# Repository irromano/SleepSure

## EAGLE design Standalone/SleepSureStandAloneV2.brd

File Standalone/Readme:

This folder includes the EAGLE files for the standalone Sleepsure circuit.

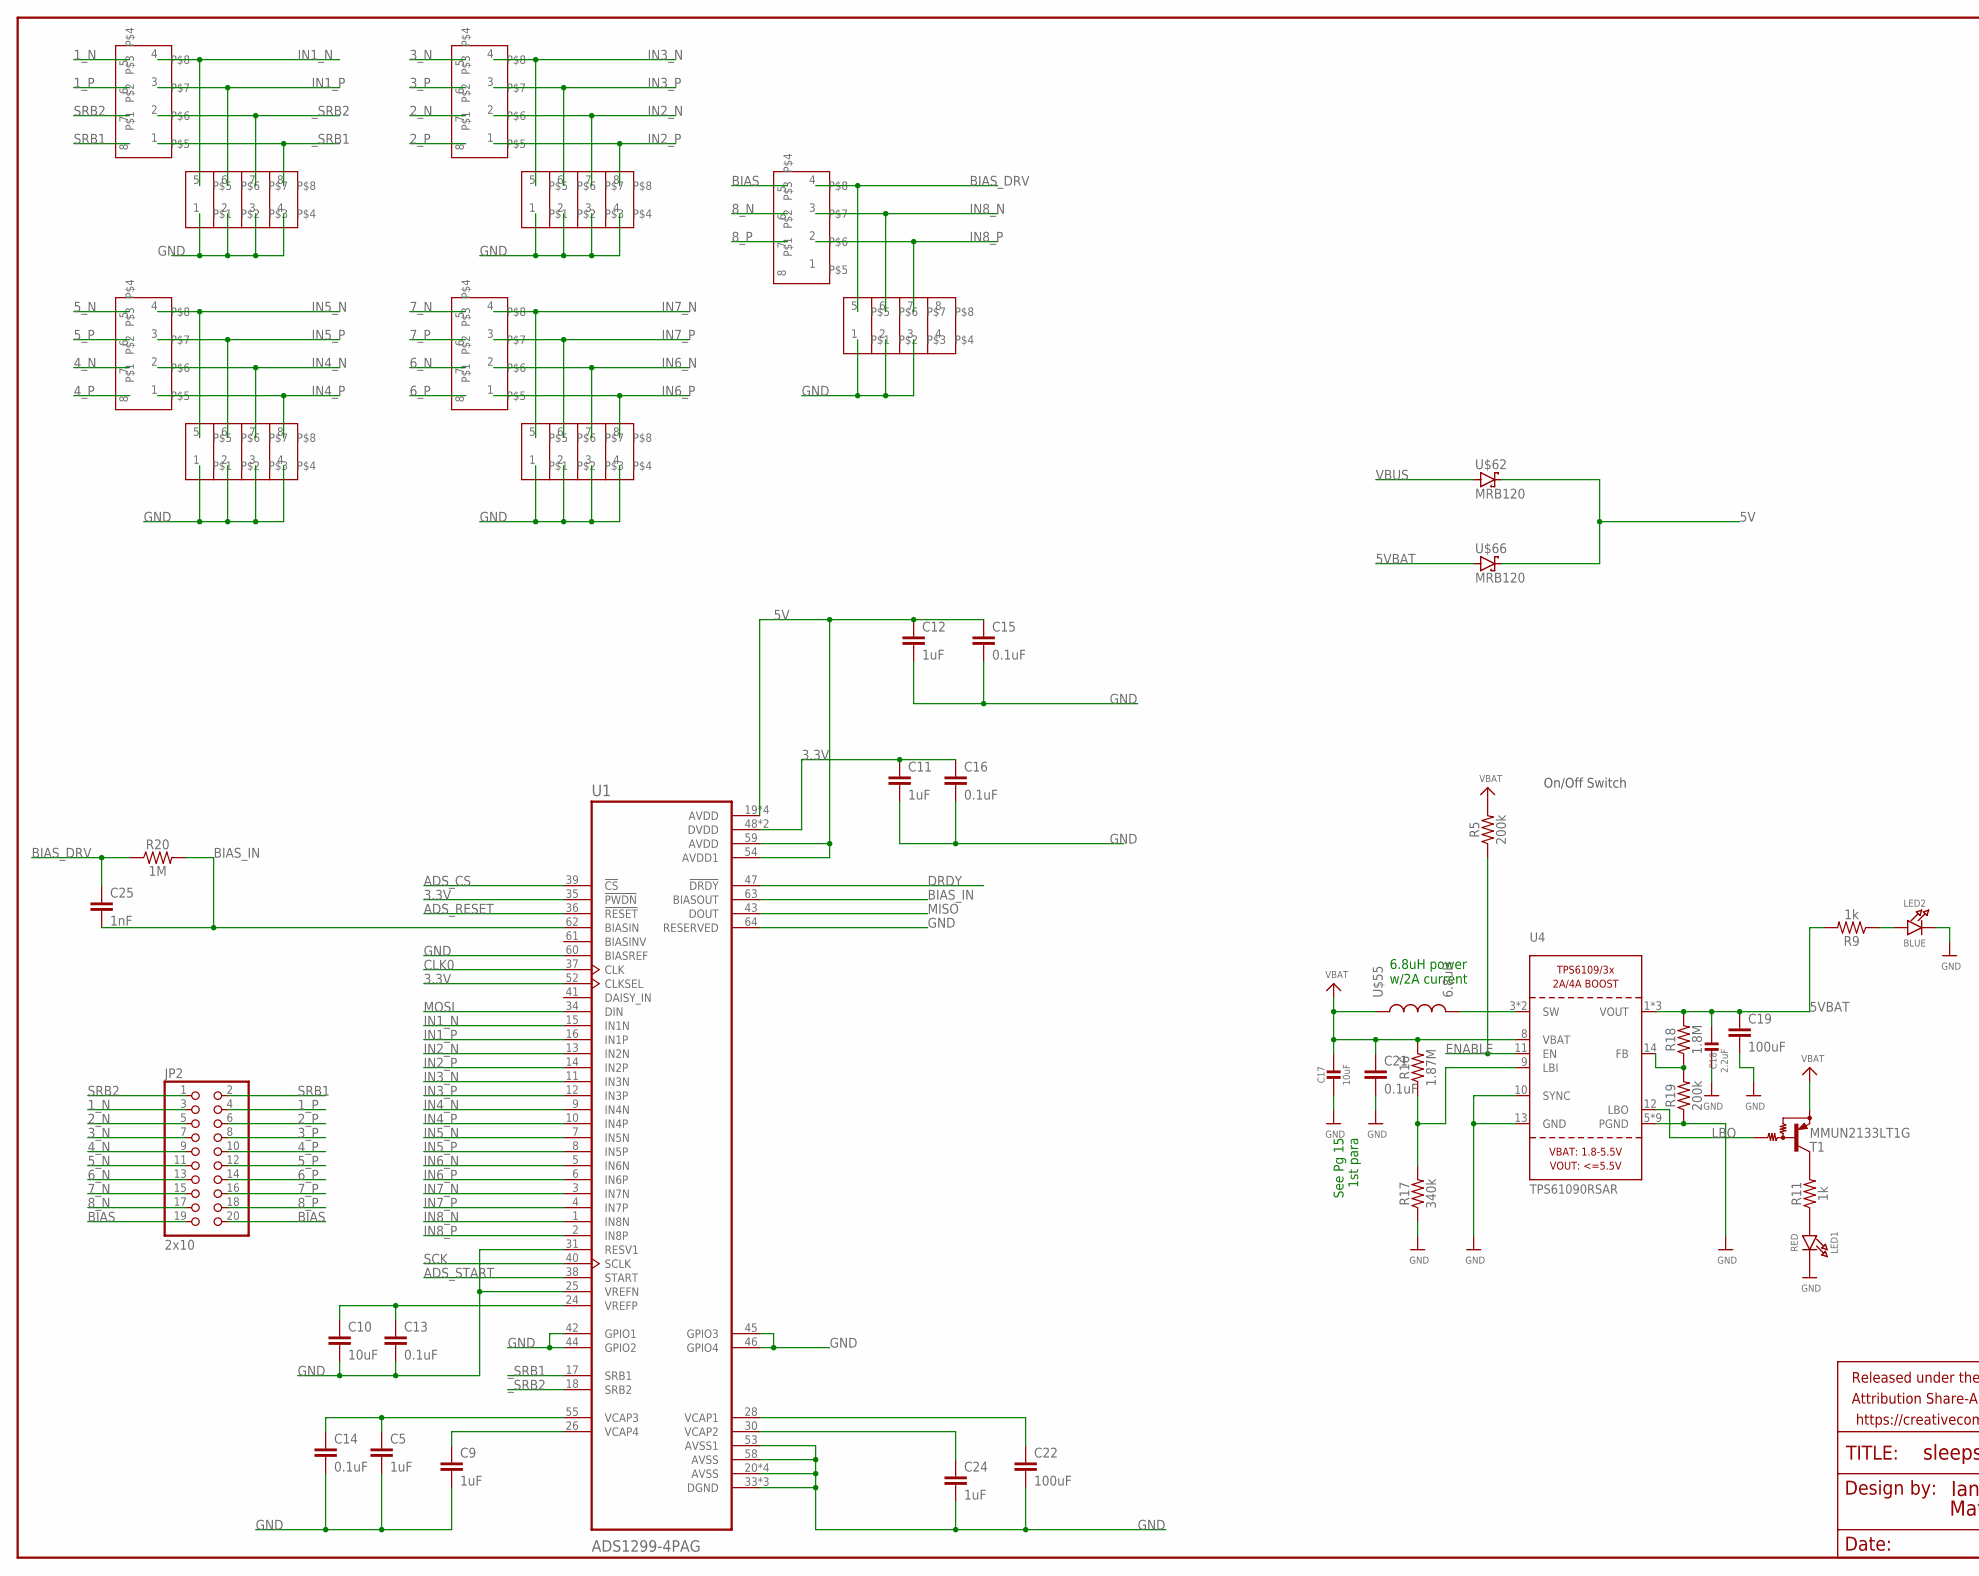
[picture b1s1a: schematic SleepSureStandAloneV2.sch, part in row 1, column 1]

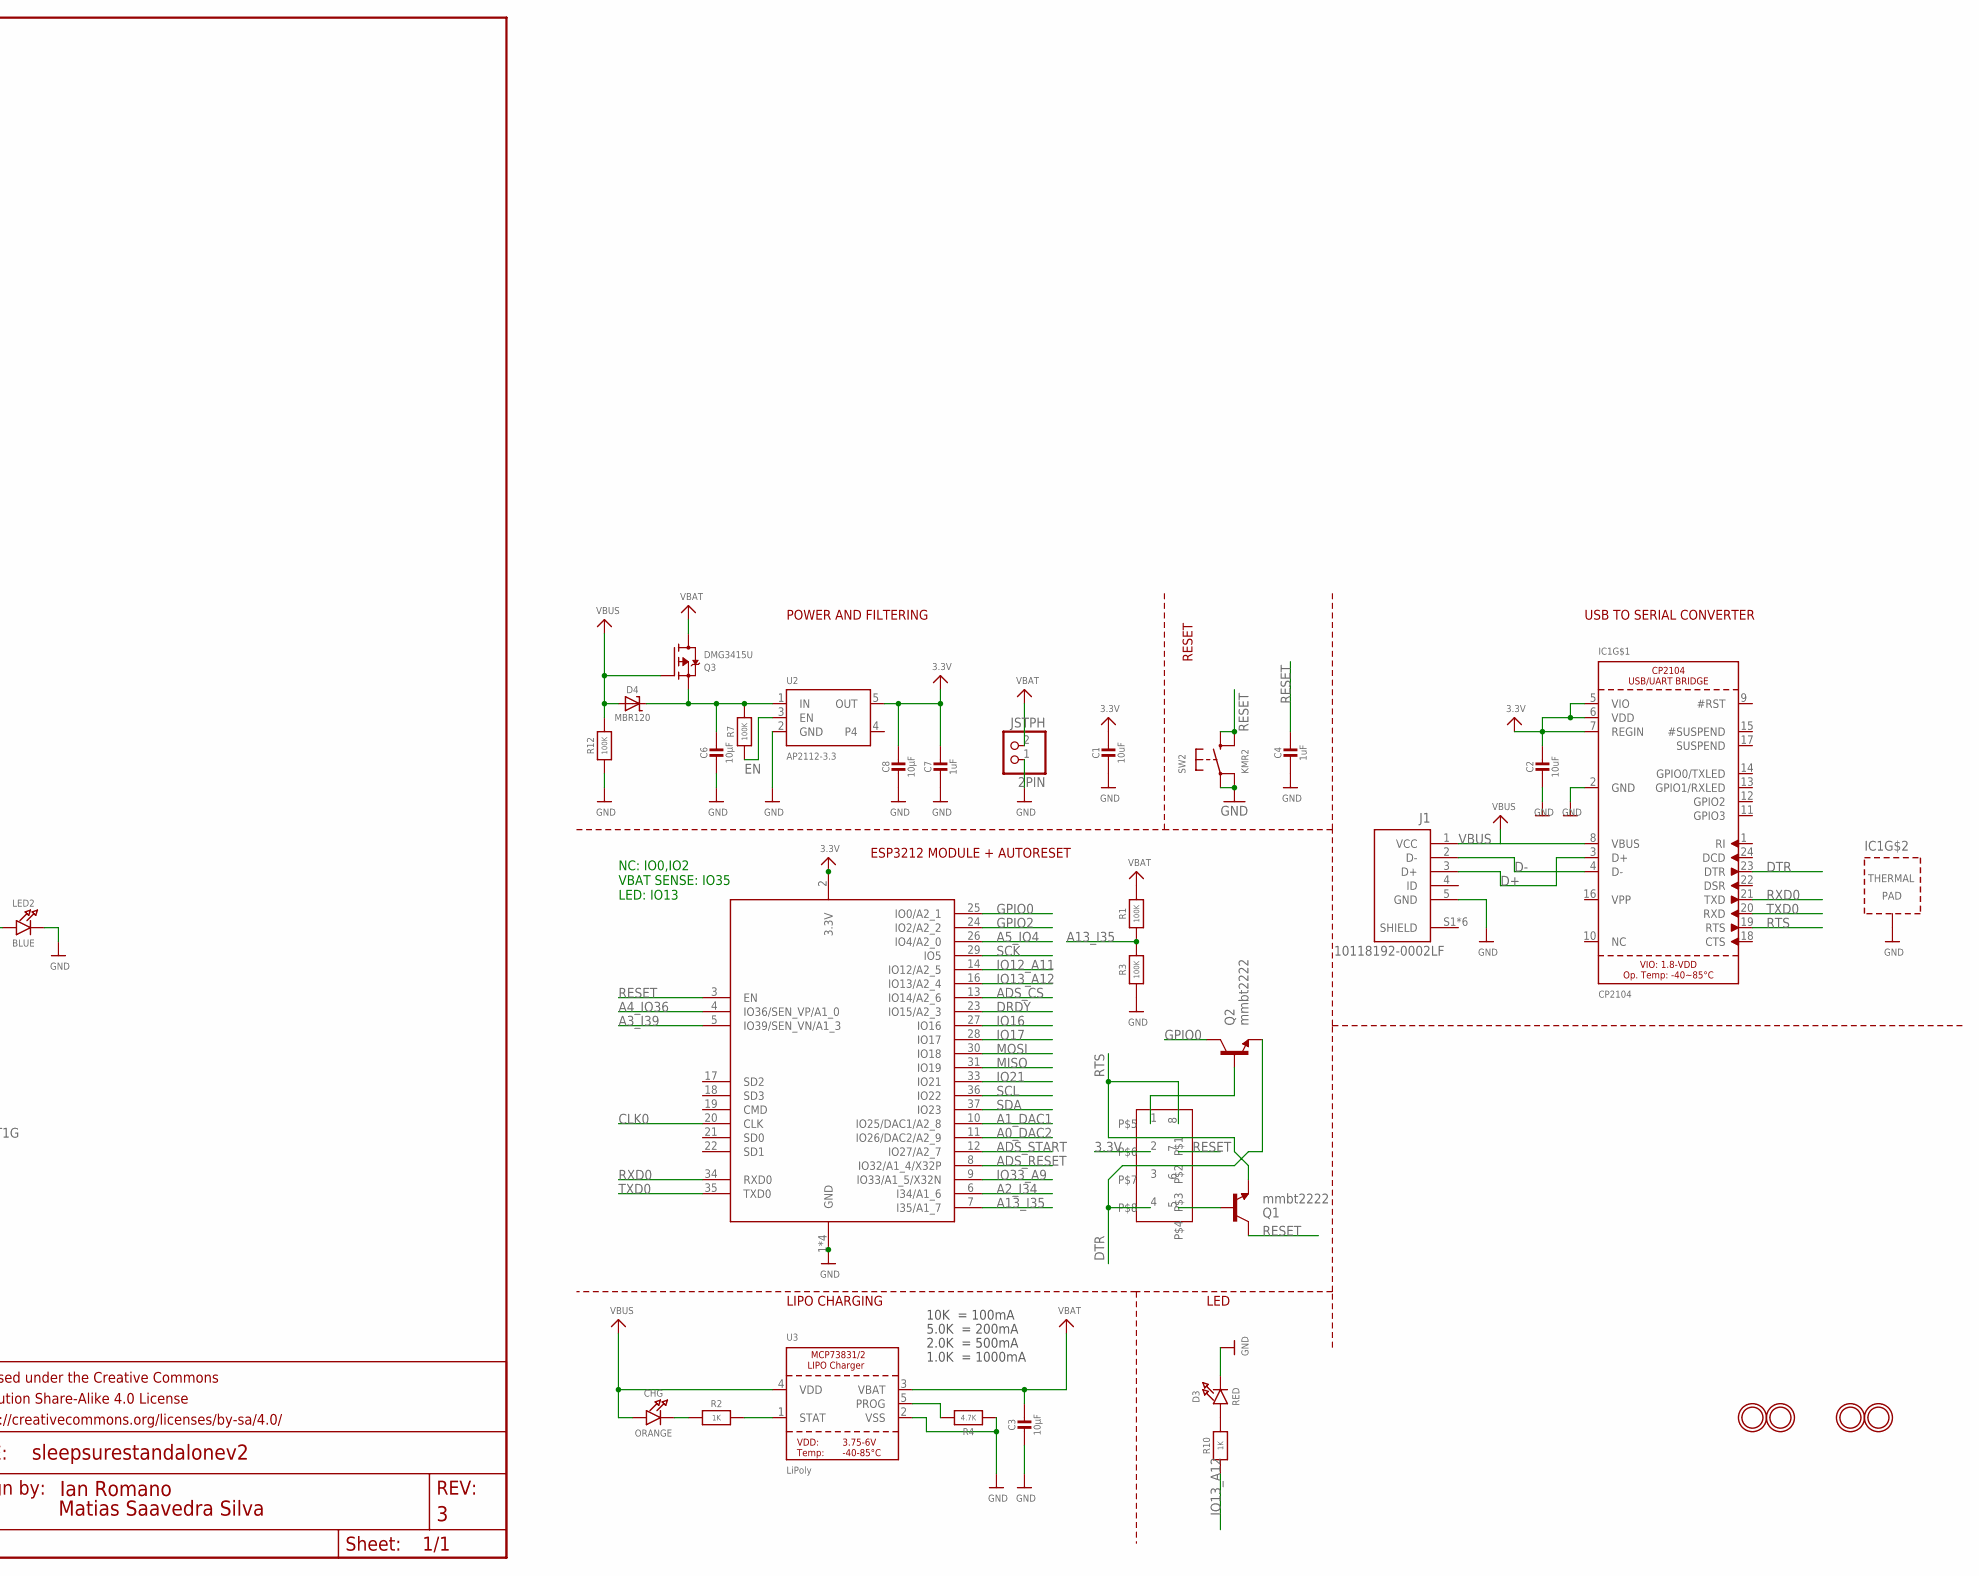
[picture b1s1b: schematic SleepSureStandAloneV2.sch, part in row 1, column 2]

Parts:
2PIN: JSTPH; JSTPH2
C1, C2, C17: 10uF; 0805-NO
C3, C6, C8: 10µF; 0805-NO
C4, C7: 1uF; 0603-NO
C5, C9, C11, C12, C24: 1uF; 0805
C10: 10uF; 0805
C13, C14, C15, C16, C21: 0.1uF; 0805
C18: 2.2uF; 0805-NO
C19, C22: 100uF; 1206
C25: 1nF; 0805
CHG: ORANGE; CHIPLED_0805_NOOUTLINE
D3: RED; CHIPLED_0805_NOOUTLINE
D4: MBR120; SOD-123
FRAME2: FRAME-LEDGER; CREATIVE_COMMONS
IC1: CP2104; QFN24_4MM_SMSC
J1: 10118192-0002LF; AMPHENOL_10118192-0002LF
JP2: 2x10; 2X09-BIG
LED1: RED; CHIPLED_0805_NOOUTLINE
LED2: BLUE; CHIPLED_0805_NOOUTLINE
Q1, Q2: mmbt2222; SOT23-3
Q3: DMG3415U; SOT23-R
R1, R3, R7, R12: 100K; 0603-NO
R2, R10: 1K; 0603-NO
R4: 4.7K; 0603-NO
R5, R19: 200k; 0805
R9, R11: 1k; 0805
R16: 1.87M; 0805
R17: 340k; 0805
R18: 1.8M; 0805
R20: 1M; 0805
SW2: KMR2; BTN_KMR2_4.6X2.8
T1: MMUN2133LT1G; SC59-BEC
U1: ADS1299-4PAG; QFP50P1200X1200X120-64N
U2: AP2112-3.3; SOT23-5
U3: LiPoly; SOT23-5
U4: TPS61090RSAR; PVQFN-16
U$6, U$19, U$31, U$32: MOUNTINGHOLE2.5; MOUNTINGHOLE_2.5_PLATED
U$7: 10k; RESCAXS50P200X100X45-8N
U$23, U$46, U$48, U$50, U$52: 1nF; CAPCAXE50P210X130X94-8N
U$44, U$45, U$47, U$49, U$51: 2.2k; RESCAXS50P200X100X45-8N
U$55: 6.8uH; 0628
U$62, U$66: MRB120; SOD123FL
X2: ESP32_WROOM32_SKINNY; WROOM32_SKINNY

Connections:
1_N: JP2.3, U$44.5
1_P: JP2.4, U$44.6
2_N: JP2.5, U$45.7
2_P: JP2.6, U$45.8
3.3V: C1.1, C2.1, C7.1, C8.1, C11.1, C16.1, IC1.5 (VIO), IC1.6 (VDD), IC1.7 (REGIN), U1.35 (!PWDN), U1.48 (DVDD), U1.50 (DVDD), U1.52 (CLKSEL), U2.5 (OUT), U$7.2, X2.2 (3.3V)
3_N: JP2.7, U$45.5
3_P: JP2.8, U$45.6
4_N: JP2.9, U$47.7
4_P: JP2.10, U$47.8
5V: C12.1, C15.1, U1.19 (AVDD), U1.21 (AVDD), U1.22 (AVDD), U1.54 (AVDD1), U1.56 (AVDD), U1.59 (AVDD), U$62.C, U$66.C
5VBAT: C18.1, C19.1, R9.2, R18.2, U4.1 (VOUT), U4.15 (VOUT), U4.16 (VOUT), U$66.A
5_N: JP2.11, U$47.5
5_P: JP2.12, U$47.6
6_N: JP2.13, U$49.7
6_P: JP2.14, U$49.8
7_N: JP2.15, U$49.5
7_P: JP2.16, U$49.6
8_N: JP2.17, U$51.6
8_P: JP2.18, U$51.7
A0_DAC2: X2.11 (IO26/DAC2/A2_9)
A1_DAC1: X2.10 (IO25/DAC1/A2_8)
A2_I34: X2.6 (I34/A1_6)
A3_I39: X2.5 (IO39/SEN_VN/A1_3)
A4_IO36: X2.4 (IO36/SEN_VP/A1_0)
A5_IO4: X2.26 (IO4/A2_0)
A13_I35: R1.1, R3.2, X2.7 (I35/A1_7)
ADS_CS: U1.39 (!CS), X2.13 (IO14/A2_6)
ADS_RESET: U1.36 (!RESET), X2.8 (IO32/A1_4/X32P)
ADS_START: U1.38 (START), X2.12 (IO27/A2_7)
BIAS: JP2.19, JP2.20, U$51.5
BIAS_DRV: C25.1, R20.1, U$51.4, U$52.5
BIAS_IN: C25.2, R20.2, U1.62 (BIASIN), U1.63 (BIASOUT)
CLK0: U1.37 (CLK), X2.20 (CLK)
D+: IC1.3 (D+), J1.3 (D+)
D-: IC1.4 (D-), J1.2 (D-)
DRDY: U1.47 (!DRDY), X2.23 (IO15/A2_3)
DTR: IC1.23 (DTR), Q2.2 (E), U$7.4
EN: R7.1, U2.3 (EN)
ENABLE: R5.1, U4.11 (EN)
GND: 2PIN.1, C1.2, C2.2, C3.2, C4.2, C5.2, C6.2, C7.2, C8.2, C9.2, C10.2, C11.2, C12.2, C13.2, C14.2, C15.2, C16.2, C17.2, C18.2, C19.2, C21.2, C22.2, C24.2, D3.C, IC1.2 (GND), IC1.THERM (TP), J1.5 (GND), LED1.C, LED2.C, R3.1, R4.1, R12.1, R17.1, R19.1, SW2.A, SW2.A' (P1), U1.20 (AVSS), U1.23 (AVSS), U1.25 (VREFN), U1.31 (RESV1), U1.32 (AVSS), U1.33 (DGND), U1.42 (GPIO1), U1.44 (GPIO2), U1.45 (GPIO3), U1.46 (GPIO4), U1.49 (DGND), U1.51 (DGND), U1.53 (AVSS1), U1.57 (AVSS), U1.58 (AVSS), U1.60 (BIASREF), U1.64 (RESERVED), U2.2 (GND), U3.2 (VSS), U4.5 (PGND), U4.6 (PGND), U4.7 (PGND), U4.10 (SYNC), U4.13 (GND), U4.P$18 (PGND), U4.P$19 (PGND), U4.P$20 (PGND), U4.P$21 (PGND), U4.P$22 (PGND), U4.THERMAL (PGND), U$23.1, U$23.2, U$23.3, U$23.4, U$46.1, U$46.2, U$46.3, U$46.4, U$48.1, U$48.2, U$48.3, U$48.4, U$50.1, U$50.2, U$50.3, U$50.4, U$52.1, U$52.2, U$52.3, X2.1 (GND), X2.15 (GND), X2.38 (GND), X2.P$1 (GND)
GPIO0: Q2.3 (C), X2.25 (IO0/A2_1)
GPIO2: X2.24 (IO2/A2_2)
IN1_N: U1.15 (IN1N), U$23.5, U$44.4
IN1_P: U1.16 (IN1P), U$23.6, U$44.3
IN2_N: U1.13 (IN2N), U$45.2, U$46.7
IN2_P: U1.14 (IN2P), U$45.1, U$46.8
IN3_N: U1.11 (IN3N), U$45.4, U$46.5
IN3_P: U1.12 (IN3P), U$45.3, U$46.6
IN4_N: U1.9 (IN4N), U$47.2, U$48.7
IN4_P: U1.10 (IN4P), U$47.1, U$48.8
IN5_N: U1.7 (IN5N), U$47.4, U$48.5
IN5_P: U1.8 (IN5P), U$47.3, U$48.6
IN6_N: U1.5 (IN6N), U$49.2, U$50.7
IN6_P: U1.6 (IN6P), U$49.1, U$50.8
IN7_N: U1.3 (IN7N), U$49.4, U$50.5
IN7_P: U1.4 (IN7P), U$49.3, U$50.6
IN8_N: U1.1 (IN8N), U$51.3, U$52.6
IN8_P: U1.2 (IN8P), U$51.2, U$52.7
IO12_A11: X2.14 (IO12/A2_5)
IO13_A12: R10.1, X2.16 (IO13/A2_4)
IO16: X2.27 (IO16)
IO17: X2.28 (IO17)
IO21: X2.33 (IO21)
IO33_A9: X2.9 (IO33/A1_5/X32N)
LBO: T1.B, U4.12 (LBO)
MISO: U1.43 (DOUT), X2.31 (IO19)
MOSI: U1.34 (DIN), X2.30 (IO18)
unnamed: CHG.C, R2.1
unnamed: Q2.1 (B), U$7.1
unnamed: R2.2, U3.1 (STAT)
unnamed: R4.2, U3.5 (PROG)
unnamed: D3.A, R10.2
unnamed: Q1.1 (B), U$7.5
unnamed: C6.1, D4.C, Q3.2 (S), R7.2, U2.1 (IN)
unnamed: C24.1, U1.30 (VCAP2)
unnamed: C22.1, U1.28 (VCAP1)
unnamed: C10.1, C13.1, U1.24 (VREFP)
unnamed: C5.1, C14.1, U1.55 (VCAP3)
unnamed: C9.1, U1.26 (VCAP4)
unnamed: U4.3 (SW), U4.4 (SW), U$55.P$2 (2)
unnamed: R16.1, R17.2, U4.9 (LBI)
unnamed: R18.1, R19.2, U4.14 (FB)
unnamed: LED2.A, R9.1
unnamed: LED1.A, R11.1
unnamed: R11.2, T1.C
RESET: C4.1, Q1.3 (C), SW2.B (S), SW2.B' (S1), U$7.7, X2.3 (EN)
RTS: IC1.19 (RTS), Q1.2 (E), U$7.8
RXD0: IC1.21 (TXD), X2.34 (RXD0)
SCK: U1.40 (SCLK), X2.29 (IO5)
SCL: X2.36 (IO22)
SDA: X2.37 (IO23)
SRB1: JP2.2, U$44.8
SRB2: JP2.1, U$44.7
TXD0: IC1.20 (RXD), X2.35 (TXD0)
VBAT: 2PIN.2, C3.1, C17.1, C21.1, Q3.3 (D), R1.2, R5.2, R16.2, T1.E, U3.3 (VBAT), U4.8 (VBAT), U$55.P$1 (1)
VBUS: CHG.A, D4.A, IC1.8 (VBUS), J1.1 (VCC), Q3.1 (G), R12.2, U3.4 (VDD), U$62.A
_SRB1: U1.17 (SRB1), U$23.8, U$44.1
_SRB2: U1.18 (SRB2), U$23.7, U$44.2

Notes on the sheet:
POWER AND FILTERING
RESET
10K = 100mA
5.0K = 200mA
2.0K = 500mA
1.0K = 1000mA
USB TO SERIAL CONVERTER
LIPO CHARGING
LED
ESP3212 MODULE + AUTORESET
NC: IO0,IO2 VBAT SENSE: IO35 LED: IO13
On/Off Switch
See Pg 15 1st para
6.8uH power w/2A current

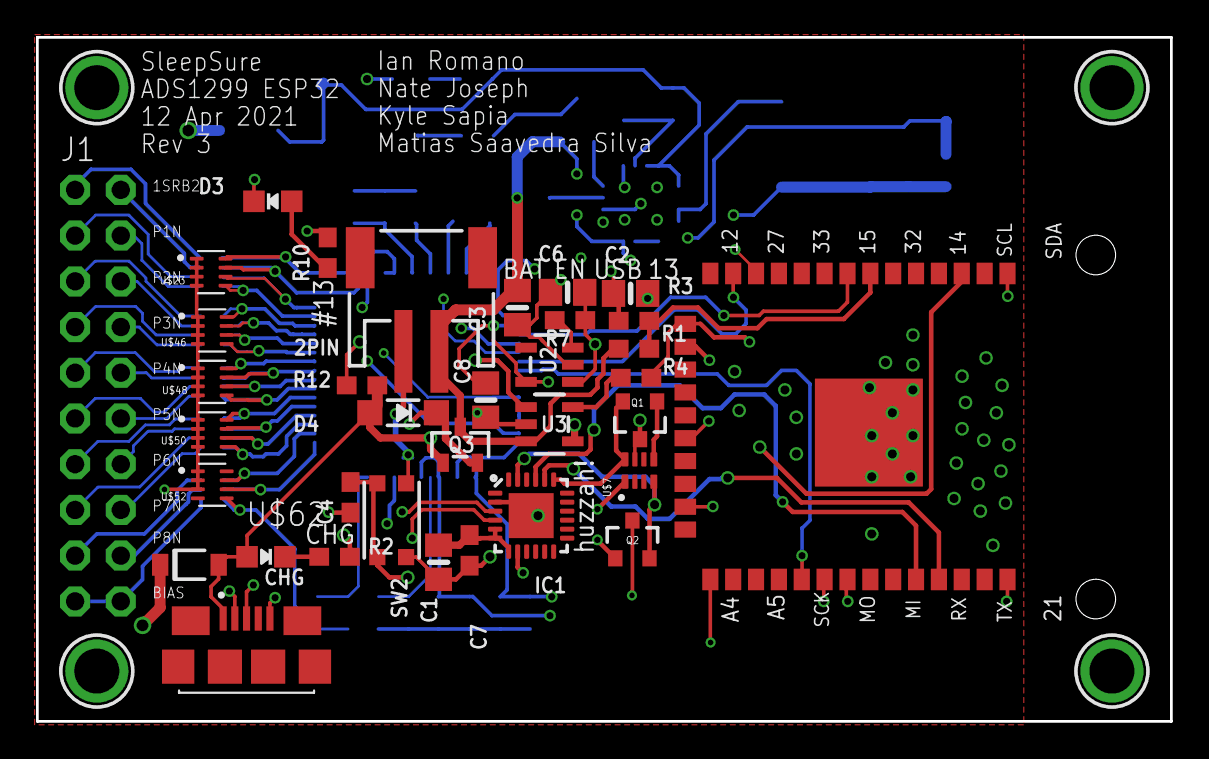
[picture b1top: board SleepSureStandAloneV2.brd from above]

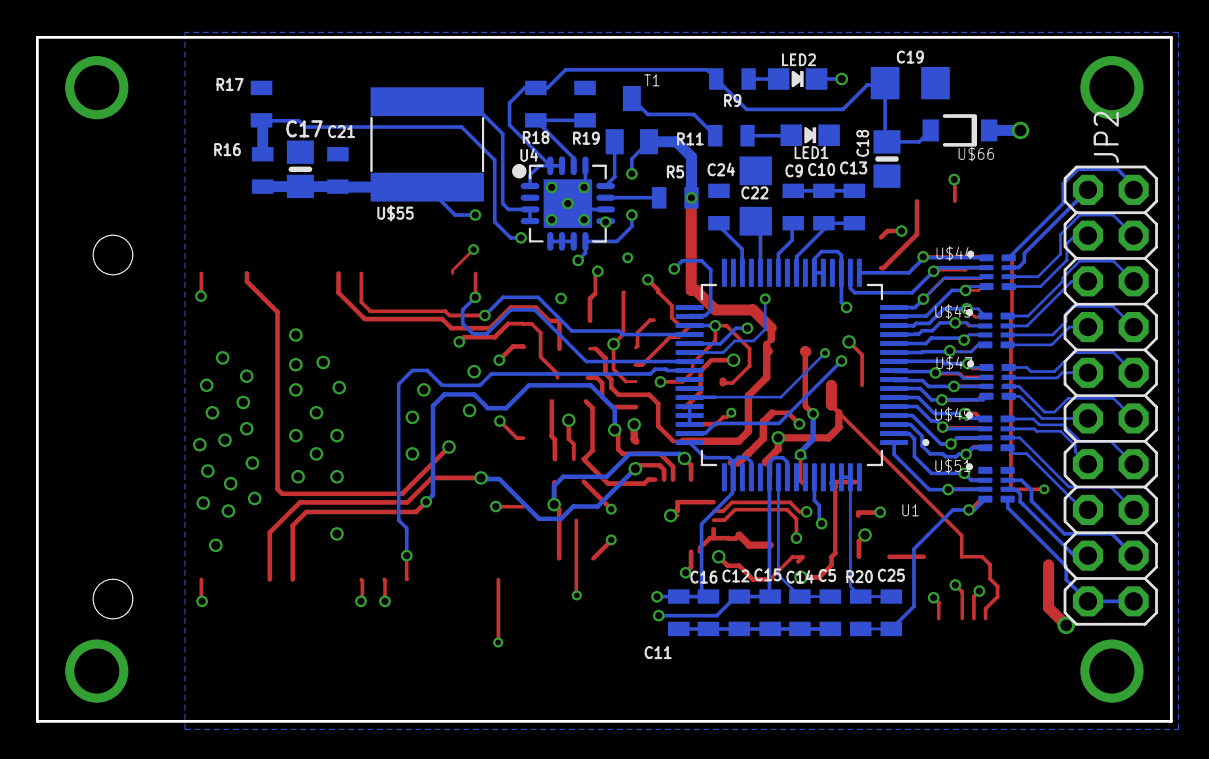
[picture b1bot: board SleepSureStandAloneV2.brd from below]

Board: 4 copper layers, 63.0 x 38.0 mm, 76 parts (37 on the bottom side), 84 nets.

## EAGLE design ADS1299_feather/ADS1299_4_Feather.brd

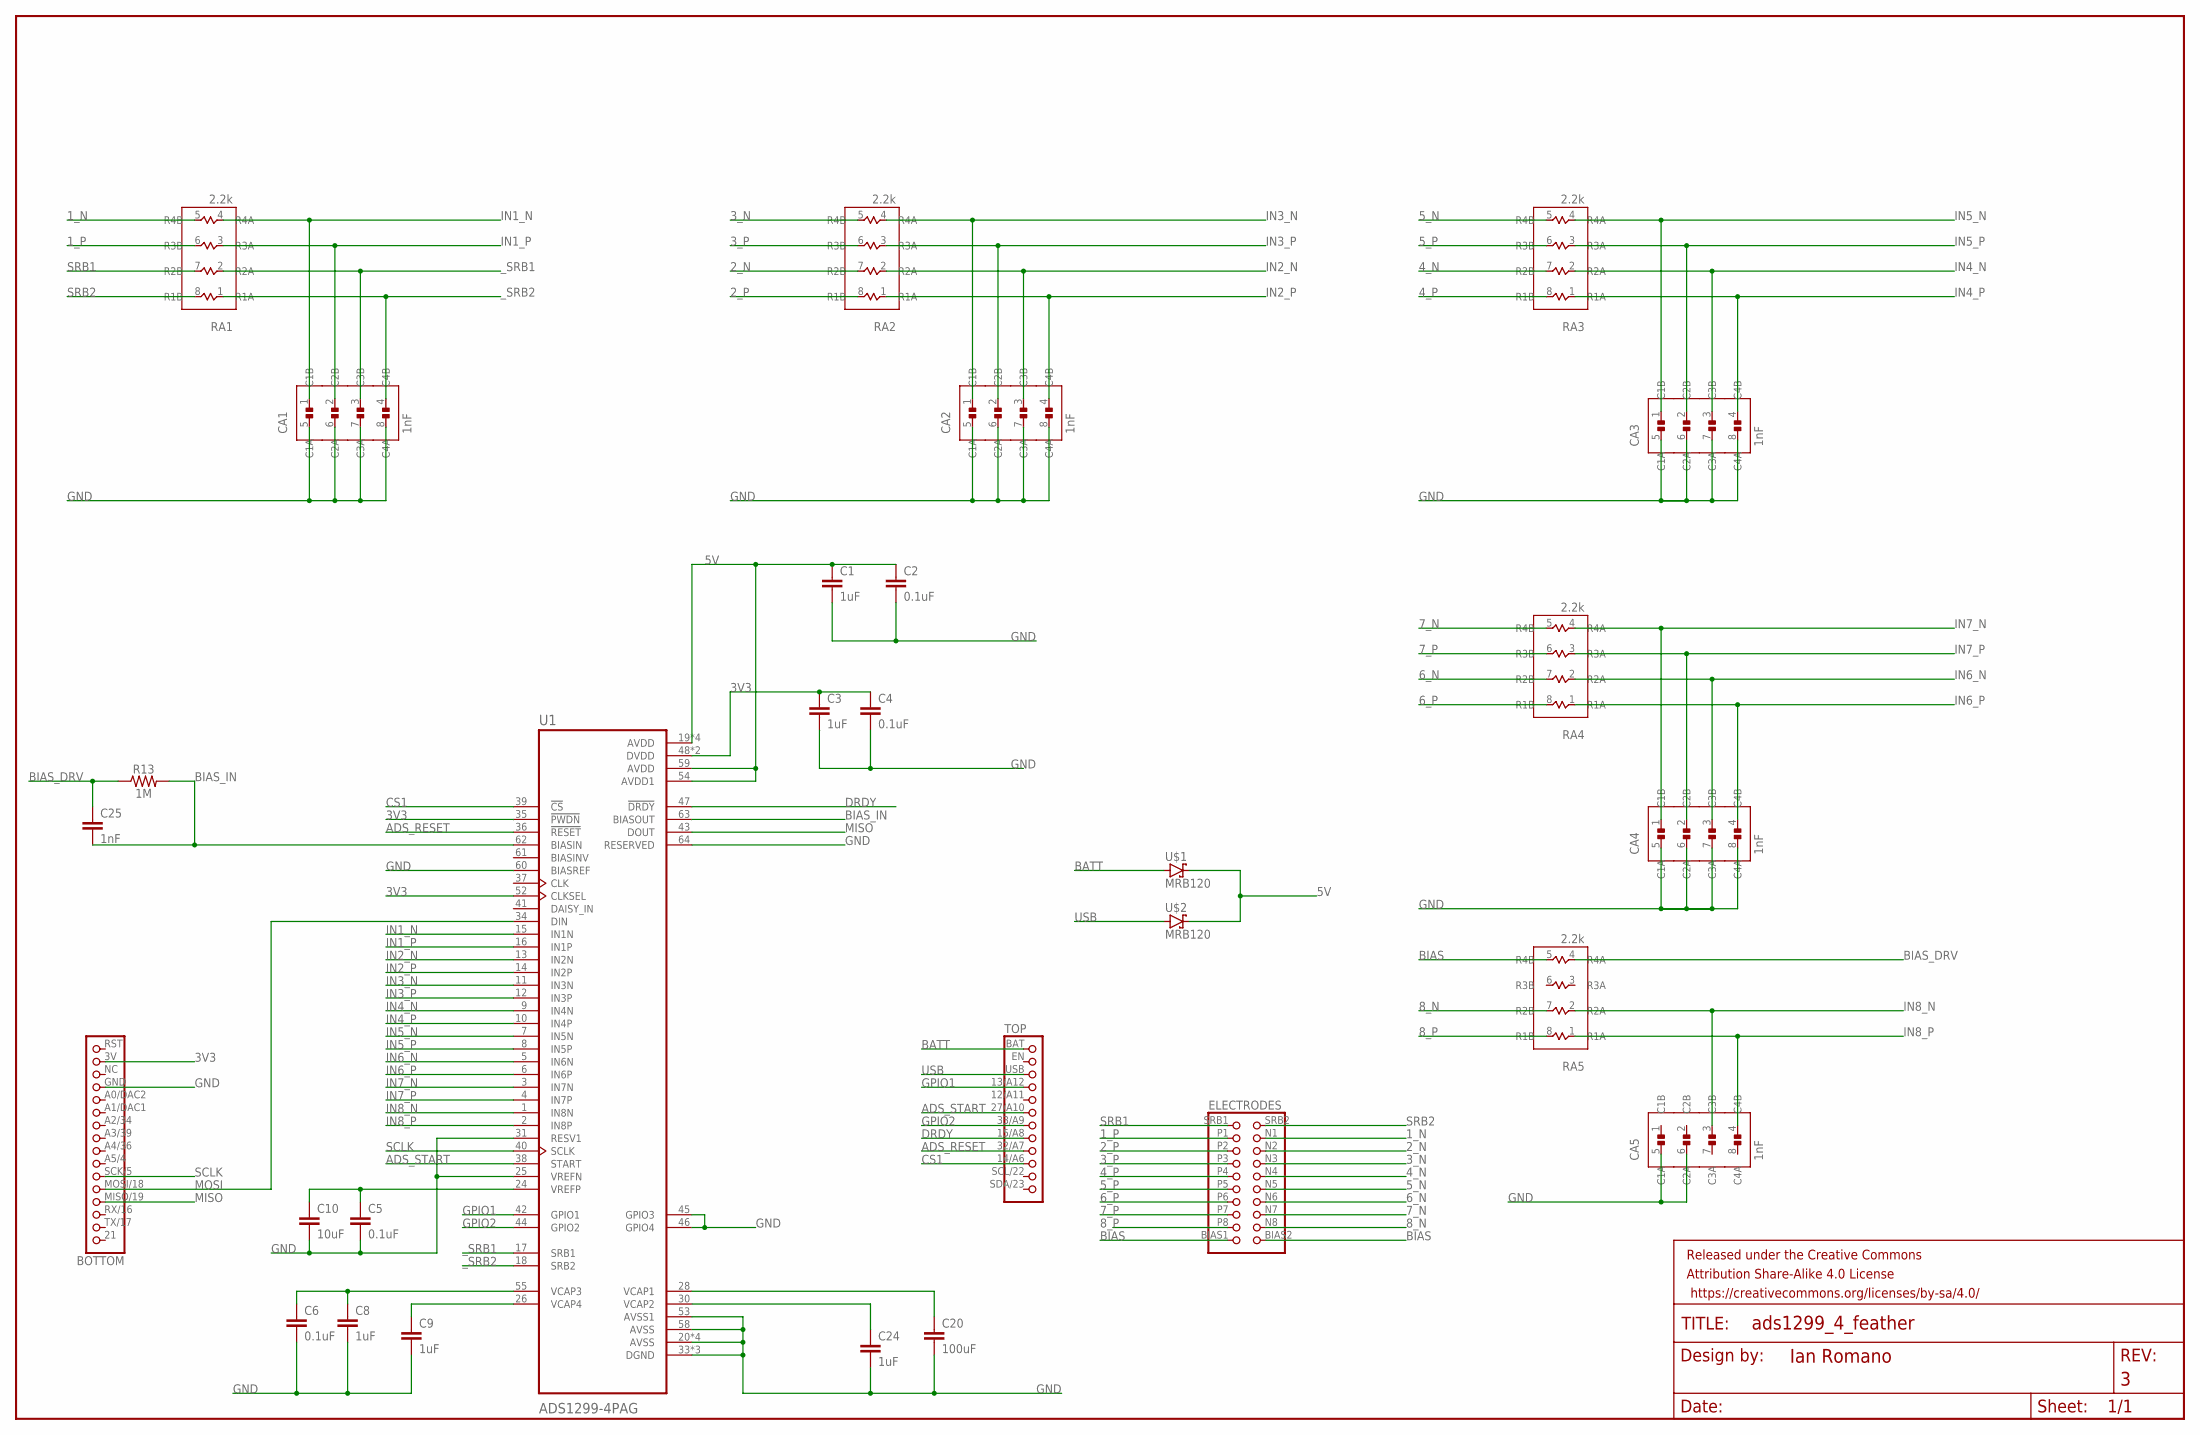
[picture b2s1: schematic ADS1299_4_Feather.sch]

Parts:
BOTTOM: MICROBUILDER_HEADER-1X16_76MIL; MICROBUILDER_1X16_ROUND_76MIL
C1, C3, C8, C9, C24: 1uF; 0805
C2, C4, C5, C6: 0.1uF; 0805
C10: 10uF; 0805
C20: 100uF; 0805
C25: 1nF; 0805
CA1, CA2, CA3, CA4, CA5: 1nF; SLEEPSURELIB_CAPCAXE50P210X130X94-8N
ELECTRODES: SLEEPSURELIB_PINHD-2X10-BIG; SLEEPSURELIB_2X10-BIG
FRAME1: FRAME-LEDGER; CREATIVE_COMMONS
R13: 1M; 0805
RA1, RA2, RA3, RA4, RA5: 2.2k; SLEEPSURELIB_RESCAXS50P200X100X45-8N
TOP: MICROBUILDER_HEADER-1X1276MIL; MICROBUILDER_1X12_ROUND_76MIL
U1: ADS1299-4PAG; QFP50P1200X1200X120-64N
U$1, U$2: MRB120; SOD123FL

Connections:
1_N: ELECTRODES.N1, RA1.5 (R4B)
1_P: ELECTRODES.P1, RA1.6 (R3B)
2_N: ELECTRODES.N2, RA2.7 (R2B)
2_P: ELECTRODES.P2, RA2.8 (R1B)
3V3: BOTTOM.3V, C3.1, C4.1, U1.35 (!PWDN), U1.48 (DVDD), U1.50 (DVDD), U1.52 (CLKSEL)
3_N: ELECTRODES.N3, RA2.5 (R4B)
3_P: ELECTRODES.P3, RA2.6 (R3B)
4_N: ELECTRODES.N4, RA3.7 (R2B)
4_P: ELECTRODES.P4, RA3.8 (R1B)
5V: C1.1, C2.1, U1.19 (AVDD), U1.21 (AVDD), U1.22 (AVDD), U1.54 (AVDD1), U1.56 (AVDD), U1.59 (AVDD), U$1.C, U$2.C
5_N: ELECTRODES.N5, RA3.5 (R4B)
5_P: ELECTRODES.P5, RA3.6 (R3B)
6_N: ELECTRODES.N6, RA4.7 (R2B)
6_P: ELECTRODES.P6, RA4.8 (R1B)
7_N: ELECTRODES.N7, RA4.5 (R4B)
7_P: ELECTRODES.P7, RA4.6 (R3B)
8_N: ELECTRODES.N8, RA5.7 (R2B)
8_P: ELECTRODES.P8, RA5.8 (R1B)
ADS_RESET: TOP.32/A7 (32), U1.36 (!RESET)
ADS_START: TOP.27/A10 (27), U1.38 (START)
BATT: TOP.BAT, U$1.A
BIAS: ELECTRODES.BIAS1, ELECTRODES.BIAS2, RA5.5 (R4B)
BIAS_DRV: C25.1, R13.1, RA5.4 (R4A)
BIAS_IN: C25.2, R13.2, U1.62 (BIASIN), U1.63 (BIASOUT)
CS1: TOP.14/A6 (14), U1.39 (!CS)
DRDY: TOP.15/A8 (15), U1.47 (!DRDY)
GND: BOTTOM.GND, C1.2, C2.2, C3.2, C4.2, C5.2, C6.2, C8.2, C9.2, C10.2, C20.2, C24.2, CA1.5 (C1A), CA1.6 (C2A), CA1.7 (C3A), CA1.8 (C4A), CA2.5 (C1A), CA2.6 (C2A), CA2.7 (C3A), CA2.8 (C4A), CA3.5 (C1A), CA3.6 (C2A), CA3.7 (C3A), CA3.8 (C4A), CA4.5 (C1A), CA4.6 (C2A), CA4.7 (C3A), CA4.8 (C4A), CA5.5 (C1A), CA5.6 (C2A), U1.20 (AVSS), U1.23 (AVSS), U1.25 (VREFN), U1.31 (RESV1), U1.32 (AVSS), U1.33 (DGND), U1.45 (GPIO3), U1.46 (GPIO4), U1.49 (DGND), U1.51 (DGND), U1.53 (AVSS1), U1.57 (AVSS), U1.58 (AVSS), U1.60 (BIASREF), U1.64 (RESERVED)
GPIO1: TOP.13/A12 (13), U1.42 (GPIO1)
GPIO2: TOP.33/A9 (33), U1.44 (GPIO2)
IN1_N: CA1.1 (C1B), RA1.4 (R4A), U1.15 (IN1N)
IN1_P: CA1.2 (C2B), RA1.3 (R3A), U1.16 (IN1P)
IN2_N: CA2.3 (C3B), RA2.2 (R2A), U1.13 (IN2N)
IN2_P: CA2.4 (C4B), RA2.1 (R1A), U1.14 (IN2P)
IN3_N: CA2.1 (C1B), RA2.4 (R4A), U1.11 (IN3N)
IN3_P: CA2.2 (C2B), RA2.3 (R3A), U1.12 (IN3P)
IN4_N: CA3.3 (C3B), RA3.2 (R2A), U1.9 (IN4N)
IN4_P: CA3.4 (C4B), RA3.1 (R1A), U1.10 (IN4P)
IN5_N: CA3.1 (C1B), RA3.4 (R4A), U1.7 (IN5N)
IN5_P: CA3.2 (C2B), RA3.3 (R3A), U1.8 (IN5P)
IN6_N: CA4.3 (C3B), RA4.2 (R2A), U1.5 (IN6N)
IN6_P: CA4.4 (C4B), RA4.1 (R1A), U1.6 (IN6P)
IN7_N: CA4.1 (C1B), RA4.4 (R4A), U1.3 (IN7N)
IN7_P: CA4.2 (C2B), RA4.3 (R3A), U1.4 (IN7P)
IN8_N: CA5.3 (C3B), RA5.2 (R2A), U1.1 (IN8N)
IN8_P: CA5.4 (C4B), RA5.1 (R1A), U1.2 (IN8P)
MISO: BOTTOM.MISO/19 (MISO), U1.43 (DOUT)
MOSI: BOTTOM.MOSI/18 (MOSI), U1.34 (DIN)
unnamed: C5.1, C10.1, U1.24 (VREFP)
unnamed: C24.1, U1.30 (VCAP2)
unnamed: C6.1, C8.1, U1.55 (VCAP3)
unnamed: C20.1, U1.28 (VCAP1)
unnamed: C9.1, U1.26 (VCAP4)
SCLK: BOTTOM.SCK/5 (SCK), U1.40 (SCLK)
SRB1: ELECTRODES.SRB1, RA1.7 (R2B)
SRB2: ELECTRODES.SRB2, RA1.8 (R1B)
USB: TOP.USB, U$2.A
_SRB1: CA1.3 (C3B), RA1.2 (R2A), U1.17 (SRB1)
_SRB2: CA1.4 (C4B), RA1.1 (R1A), U1.18 (SRB2)

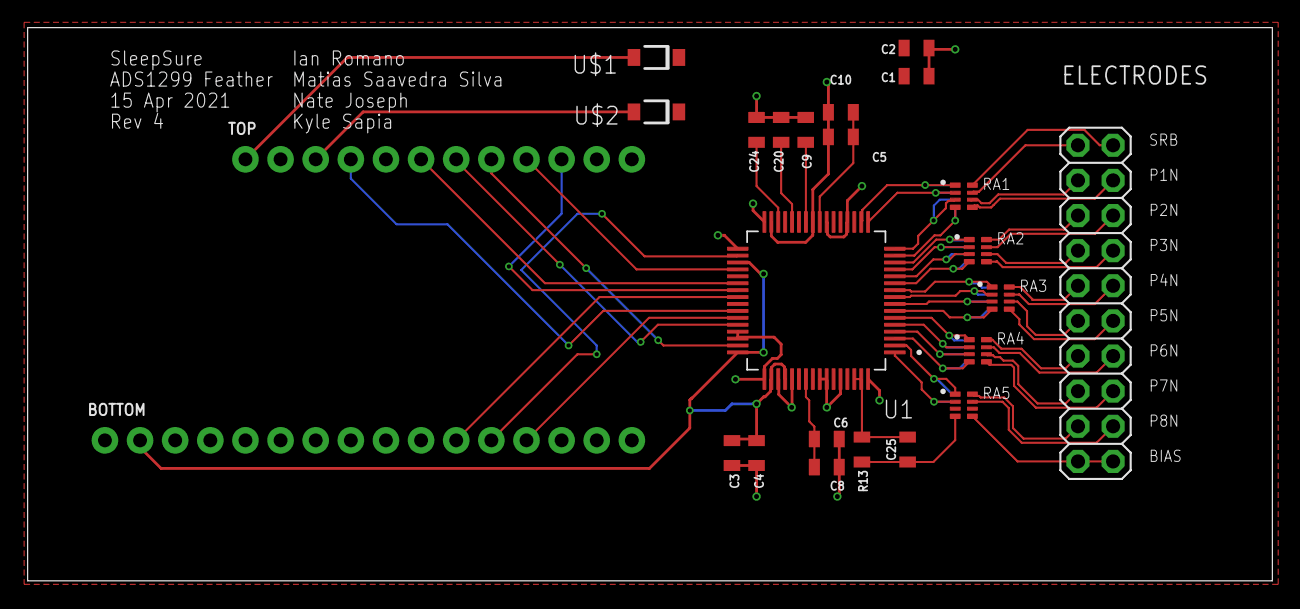
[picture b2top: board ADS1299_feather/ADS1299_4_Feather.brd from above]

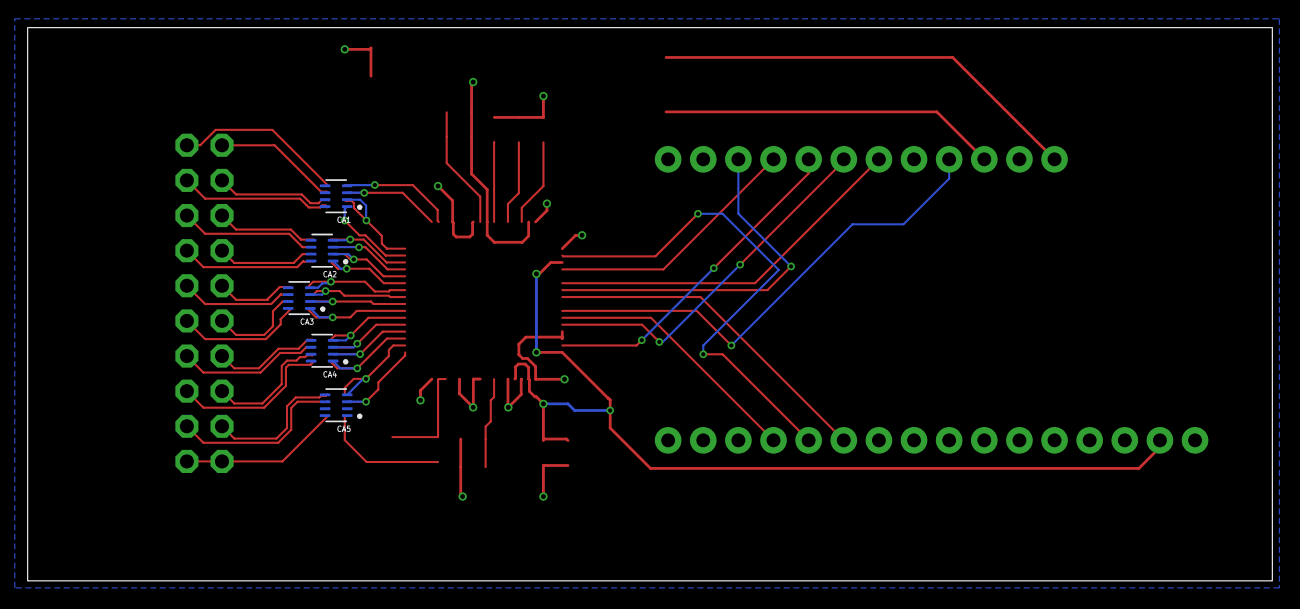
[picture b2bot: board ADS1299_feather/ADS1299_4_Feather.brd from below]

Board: 2 copper layers, 90.0 x 40.0 mm, 30 parts (5 on the bottom side), 58 nets.

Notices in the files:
parts and their libraries:
SparkFun-Capacitors: Licensing: Creative Commons ShareAlike 4.0 International - https://creativecommons.org/licenses/by-sa/4.0
SparkFun-Aesthetics: Released under the Creative Commons Attribution Share-Alike 4.0 License
SparkFun-Aesthetics: https://creativecommons.org/licenses/by-sa/4.0
